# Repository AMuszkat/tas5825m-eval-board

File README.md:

# tas5825m-eval-board

An evaluation board for the **TAS5825M Class-D audio amplifier** optimized for thermal performance for competitive benchmarking pourposes.

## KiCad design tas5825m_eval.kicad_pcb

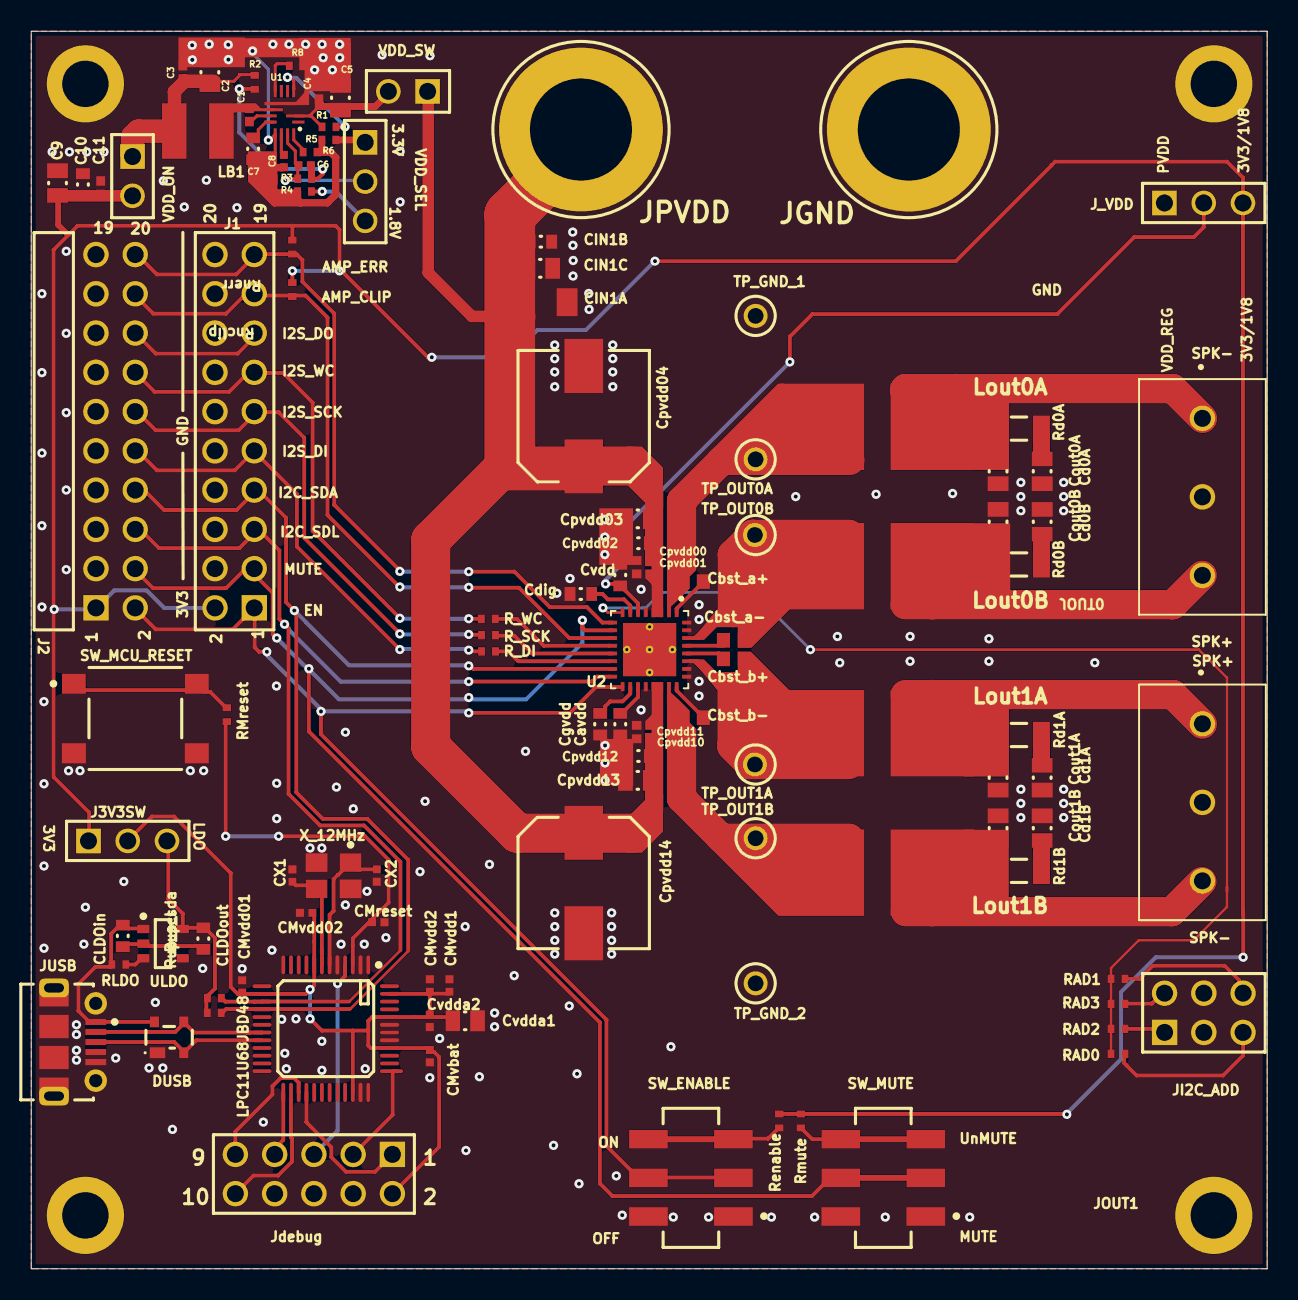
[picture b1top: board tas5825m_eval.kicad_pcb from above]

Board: 4 copper layers, 80.0 x 80.1 mm, 112 parts (0 on the bottom side), 74 nets.

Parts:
C1, C3, C4, C11: Cap; CAP0402_IPC_B
C2, C5: Cap; CAPC0805(2012)100_L
C6, C8: Cap; CAPC0402(1005)60_L
C7, C10: Cap; CAPC0603(1608)100_L
C9: Cap; CAPC0805(2012)145_L
CIN1A: NP 1206; CAP1206_IPC_B
CIN1B: NP 2106; CAPC0603(1608)100_L
CIN1C: NP 0805; CAPC0805(2012)145_L
CLDOin: Cap; CAPC0603(1608)100_L
CLDOout: Cap; CAPC0603(1608)100_L
CMreset: Cap; CAPC0402(1005)60_L
CMvbat: Cap; CAPC0402(1005)60_L
CMvdd01, CMvdd1, CMvdd02: Cap; CAPC0402(1005)60_L
CMvdd2: 10nF 25V X7R 0402; CAPC0402(1005)60_L
CX1, CX2: Cap; CAPC0402(1005)60_L
Cavdd: Cap; CAPC0603(1608)100_L
Cbst_a+: CAP; CAP0603_IPC_B
Cbst_a-: CAP; CAP0603_IPC_B
Cbst_b+: CAP; CAP0603_IPC_B
Cbst_b-: CAP; CAP0603_IPC_B
Cd0A, Cd0B, Cd1A, Cd1B: NP 0805; CAPC0805(2012)145_L
Cdig: Cap; CAPC0603(1608)100_L
Cgvdd: Cap; CAPC0603(1608)100_L
Cout0A, Cout0B, Cout1A, Cout1B: Cap; CAPC0805(2012)145_L
Cpvdd00, Cpvdd01, Cpvdd10, Cpvdd11: Cap; CAP0402_IPC_B
Cpvdd02, Cpvdd12: Cap; CAPC0603(1608)100_L
Cpvdd03, Cpvdd13: Cap; CAPC0805(2012)145_L
Cpvdd04, Cpvdd14: Cap; NIC-CAPA2-8X10_V
Cvdd: Cap; CAPC0603(1608)100_L
Cvdda1: 10uF 25V X5R 0805; CAPC0805(2012)145_L
Cvdda2: Cap; CAPC0402(1005)60_L
DUSB: PRTR5V0U2X,215; NXP-SOT143B-4_V
J1: Header 10X2; 61302021121
J2: Header 10X2; 61302021021
J3V3SW: 2.54mm V Header; 61300311121
JGND: 111-2223-001; CON-PLUG-111-2223-001
JI2C_ADD: 2.54mm V Header; 61300621121
JOUT0, JOUT1: 282837-3; TE_282837-3
JPVDD: 111-2223-001; CON-PLUG-111-2223-001
JUSB: 105017-0001; USB-MICRO-B_V
J_VDD: 2.54mm V header; 61300311121
Jdebug: 2.54mm Ver 10pin; 61301021121
LB1: IND. 10uH; INDP4040X25N
LPC11U68JBD48: 32-bit MCU; CQFP50P900X900X160-48L
Lout0A, Lout0B, Lout1A, Lout1B: NP 1267AY IND; IND_1267AY_series_extended
R1, R4, R6: Cap; RESC0402(1005)_L
R2, R3, R5, R8: Res; RESC0402(1005)_L
RAD0, RAD1, RAD2, RAD3: Res; RESC0402(1005)_L
RLDO: 10K 1% 0402; RESC0402(1005)_L
RMreset: 100R 1% 0402; RESC0402(1005)_L
R_DI: Res; RESC0402(1005)_L
R_SCK: Res; RESC0402(1005)_L
R_WC: Res; RESC0402(1005)_L
Rd0A, Rd0B, Rd1A, Rd1B: NP 1206; RES1206_IPC_B
Renable: Res; RESC0402(1005)_L
Rmute: Res; RESC0402(1005)_L
Rnclip: NP 0402; RESC0402(1005)_L
Rnerr: NP 0402; RESC0402(1005)_L
Rup_scl: Res; RESC0402(1005)_L
Rup_sda: Res; RESC0402(1005)_L
SW_ENABLE: JS202011SCQN
SW_MCU_RESET: B3S-1000; OMRON-B3S-1000-4_V
SW_MUTE: JS202011SCQN
TP_GND_1, TP_GND_2: NP; KSTN-5001
TP_OUT0A, TP_OUT0B, TP_OUT1A, TP_OUT1B: NP; KSTN-5001
U1: MP2269GD-P‎; MP2269GD-P
U2: TAS5825MRHBR; TAS5825M
ULDO: LP5907MFX-3.3/NOPB; DBV0005A_L
VDD_ON: 61300211121
VDD_SEL: 61300311121
VDD_SW: 61300211121
X_12MHz: ABM8G-12.000MHZ-18-D2Y-T; ABRACON_ABM8G_V

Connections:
AGND: C7.1, C8.2, R4.1, R5.1, R6.2, U1.12
AMP_ADR: RAD0.2, RAD1.2, RAD2.1, RAD3.1, U2.8
AMP_ENABLE: J1.1, J2.2, SW_ENABLE.2, SW_ENABLE.5, U2.17
AMP_ERR: J1.19, J2.20, Rnerr.2, U2.9
AMP_MUTE: J1.3, J2.4, SW_MUTE.2, SW_MUTE.5, U2.10
AMP_WARN: J1.17, J2.18, Rnclip.2, U2.11
BOOT_L_EN: Jdebug.5, LPC11U68JBD48.4
GND: C2.1, C3.2, C4.1, C5.1, C9.2, C10.1, C11.2, CIN1A.2, CIN1B.1, CIN1C.2, CMreset.2, CMvbat.2, CMvdd1.1, CMvdd01.2, CMvdd2.1, CMvdd02.1, CX1.1, CX2.1, Cavdd.2, Cd0A.1, Cd0B.2, Cd1A.2, Cd1B.1, Cdig.2, Cgvdd.2, Cout0A.1, Cout0B.2, Cout1A.2, Cout1B.1, Cpvdd00.1, Cpvdd01.1, Cpvdd02.1, Cpvdd03.2, Cpvdd04.2, Cpvdd10.1, Cpvdd11.1, Cpvdd12.1, Cpvdd13.2, Cpvdd14.2, Cvdd.2, Cvdda1.2, Cvdda2.1, DUSB.1, J1.4, J1.6, J1.8, J1.10, J1.12, J1.14, J1.16, J1.18, J1.20, J2.3, J2.5, J2.7, J2.9, J2.11, J2.13, J2.15, J2.17, J2.19, JGND.1, JI2C_ADD.3, JI2C_ADD.4, JOUT0.2, JOUT1.2, JUSB.5, JUSB.6, JUSB.7, JUSB.8, JUSB.9, JUSB.10, JUSB.11, Jdebug.4, Jdebug.6, Jdebug.8, LPC11U68JBD48.2, LPC11U68JBD48.5, LPC11U68JBD48.35, LPC11U68JBD48.41, LPC11U68JBD48.43, R8.1, SW_ENABLE.1, SW_ENABLE.4, SW_MCU_RESET.3, SW_MCU_RESET.4, SW_MUTE.1, SW_MUTE.4, TP_GND_1.1, TP_GND_2.1, U1.3, U1.8, U2.5, U2.20, U2.25, U2.26, U2.31, U2.32, U2.33, U2.34, U2.35, U2.36, U2.37, U2.38, X_12MHz.2, X_12MHz.4
I2C_SCL: J1.5, J2.6, LPC11U68JBD48.15, Rup_sda.1, U2.16
I2C_SDA: J1.7, J2.8, LPC11U68JBD48.16, Rup_scl.1, U2.15
I2S/TDM_DI: J1.9, J2.10, R_DI.1
I2S/TDM_DO: J1.15, J2.16
I2S/TDM_SCK: J1.11, J2.12, R_SCK.1
I2S/TDM_WC: J1.13, J2.14, R_WC.1
NetC1_1: C1.1, U1.10
NetC1_2: C1.2, LB1.1, U1.9
NetC2_2: C2.2, C3.1, LB1.2, R2.2, VDD_ON.1
NetC4_2: C4.2, C5.2, R1.1, U1.2, VDD_SW.2
NetC6_1: C6.1, R2.1, R3.1
NetC6_2: C6.2, R3.2, U1.14, VDD_SEL.2
NetC7_2: C7.2, U1.11
NetC8_1: C8.1, U1.13
NetCLDOin_1: CLDOin.1, CLDOout.1, ULDO.2
NetCLDOin_2: CLDOin.2, DUSB.4, JUSB.1, RLDO.2, ULDO.1
NetCMreset_1: CMreset.1, LPC11U68JBD48.3, RMreset.2
NetCX1_2: CX1.2, LPC11U68JBD48.7, X_12MHz.3
NetCX2_2: CX2.2, LPC11U68JBD48.6, X_12MHz.1
NetCavdd_1: Cavdd.1, U2.19
NetCbst_a+_1: Cbst_a+.1, U2.1
NetCbst_a-_1: Cbst_a-.1, U2.29
NetCbst_b+_1: Cbst_b+.1, U2.28
NetCbst_b-_1: Cbst_b-.1, U2.24
NetCd0A_2: Cd0A.2, Rd0A.1
NetCd0B_1: Cd0B.1, Rd0B.1
NetCd1A_1: Cd1A.1, Rd1A.2
NetCd1B_2: Cd1B.2, Rd1B.2
NetCdig_1: Cdig.1, U2.7
NetCgvdd_1: Cgvdd.1, U2.18
NetDUSB_2: DUSB.2, JUSB.3, LPC11U68JBD48.20
NetDUSB_3: DUSB.3, JUSB.2, LPC11U68JBD48.19
NetJI2C_ADD_1: JI2C_ADD.1, RAD2.2
NetJI2C_ADD_2: JI2C_ADD.2, RAD3.2
NetJI2C_ADD_5: JI2C_ADD.5, RAD0.1
NetJI2C_ADD_6: JI2C_ADD.6, RAD1.1
NetJdebug_1: Jdebug.1, LPC11U68JBD48.28
NetJdebug_3: Jdebug.3, LPC11U68JBD48.37
NetJdebug_7: Jdebug.7, LPC11U68JBD48.25
NetJdebug_9: Jdebug.9, LPC11U68JBD48.27
NetJdebug_10: Jdebug.10, LPC11U68JBD48.26
NetR1_2: R1.2, U1.4
NetR4_2: R4.2, VDD_SEL.3
NetR5_2: R5.2, VDD_SEL.1
NetR6_1: R6.1, U1.15
NetR8_2: R8.2, U1.7
NetRLDO_1: RLDO.1, ULDO.3
NetRMreset_1: RMreset.1, SW_MCU_RESET.1, SW_MCU_RESET.2
NetR_DI_2: R_DI.2, U2.14
NetR_SCK_2: R_SCK.2, U2.13
NetR_WC_2: R_WC.2, U2.12
NetRenable_1: Renable.1, SW_ENABLE.3, SW_ENABLE.6
NetRmute_1: Rmute.1, SW_MUTE.3, SW_MUTE.6
OUT0A: Cbst_a+.2, Lout0A.2, TP_OUT0A.1, U2.2
OUT0B: Cbst_a-.2, Lout0B.2, TP_OUT0B.1, U2.30
OUT1A: Cbst_b+.2, Lout1A.1, TP_OUT1A.1, U2.27
OUT1B: Cbst_b-.2, Lout1B.1, TP_OUT1B.1, U2.23
PVDD: CIN1A.1, CIN1B.2, CIN1C.1, Cpvdd00.2, Cpvdd01.2, Cpvdd02.2, Cpvdd03.1, Cpvdd04.1, Cpvdd10.2, Cpvdd11.2, Cpvdd12.2, Cpvdd13.1, Cpvdd14.1, JPVDD.1, U2.3, U2.4, U2.21, U2.22, VDD_SW.1
SPEAK0+: Cout0A.2, JOUT0.1, Lout0A.1, Rd0A.2
SPEAK0-: Cout0B.1, JOUT0.3, Lout0B.1, Rd0B.2
SPEAK1+: Cout1A.1, JOUT1.1, Lout1A.2, Rd1A.1
SPEAK1-: Cout1B.2, JOUT1.3, Lout1B.2, Rd1B.1
VDD: Cvdd.1, J_VDD.2, U2.6
VDD_BUCK: C9.1, C10.2, C11.1, J1.2, J2.1, J3V3SW.1, J_VDD.3, Renable.2, Rmute.2, Rnclip.1, Rnerr.1, VDD_ON.2
VDD_LDO: CLDOout.2, J3V3SW.3, Rup_scl.2, Rup_sda.2, ULDO.5
VDD_MCU: CMvbat.1, CMvdd01.1, CMvdd1.2, CMvdd2.2, CMvdd02.2, Cvdda1.1, Cvdda2.2, J3V3SW.2, Jdebug.2, LPC11U68JBD48.8, LPC11U68JBD48.14, LPC11U68JBD48.34, LPC11U68JBD48.40, LPC11U68JBD48.44, LPC11U68JBD48.47
